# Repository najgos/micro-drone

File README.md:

# DR3 – micro quadcopter with a custom flight controller

A micro quadcopter I designed and built from scratch: my own flight controller PCB designed in KiCad,
flight firmware for the Seeed XIAO ESP32-C6, and a hand-held ESP32 remote linked over ESP-NOW.

**Tech:** KiCad · 2-layer PCB design · C++ · ESP32 / ESP32-C6 · ESP-NOW · MPU6050 over I²C ·
sensor fusion · cascaded PID control

## System overview

| Part | Hardware | Role |
|---|---|---|
| Drone | Custom PCB: Seeed XIAO ESP32-C6, MPU6050 IMU, 4 MOSFET motor channels | Attitude estimation, cascaded PID control, motor PWM, arming logic |
| Remote | ESP32 Dev Module, 2 analog joysticks with ARM / KILL buttons | Reads the sticks and sends control frames over ESP-NOW |

## Hardware – controller PCB

- 2-layer PCB, approx. 45.5 × 51 mm, designed in KiCad (schematic, layout, Gerber files)
- 4 motor channels, each with an N-MOSFET (SOT-23) and an SS14 diode
- Seeed XIAO ESP32-C6 module and MPU6050 (GY-521) IMU over I²C
- 0805 / SOT-23 / SMA footprints; design and production files in [`dr3/`](dr3)

## Firmware

One Arduino sketch for both boards in [`firmware/dr3/`](firmware/dr3). The role is chosen automatically
from the selected board: **XIAO_ESP32C6 → drone**, **ESP32 Dev Module → remote**.

- **Attitude estimation:** gyro and accelerometer fusion in the FRD body frame
- **Control:** angle P loop → angular-rate PID (filtered derivative on measurement, anti-windup), X-frame mixer
- **Arming and stop conditions:** state machine (locked / disarmed / armed / fault); arming only at zero
  throttle with centred sticks; motors stop on KILL, link loss, IMU fault, excessive tilt or USB connection
- **Radio:** ESP-NOW control frames with a project ID and sequence numbers; the drone accepts frames only
  from the first remote it hears and only newer than the previous one
- **Calibration at power-up:** the remote averages the stick centres, the drone averages 200 gyro samples
  to obtain the gyro bias
- **Status LED:** fault, armed, ready to arm, waiting

## Technical details

Built with Arduino-ESP32 3.3.x. Pins, radio settings, IMU mounting and controller gains are in
[`config.h`](firmware/dr3/config.h).

```
firmware/dr3/   drone and remote firmware (C++)
dr3/            KiCad project and Gerber files
docs/images/    photos, flight GIF and the KiCad screenshot
```

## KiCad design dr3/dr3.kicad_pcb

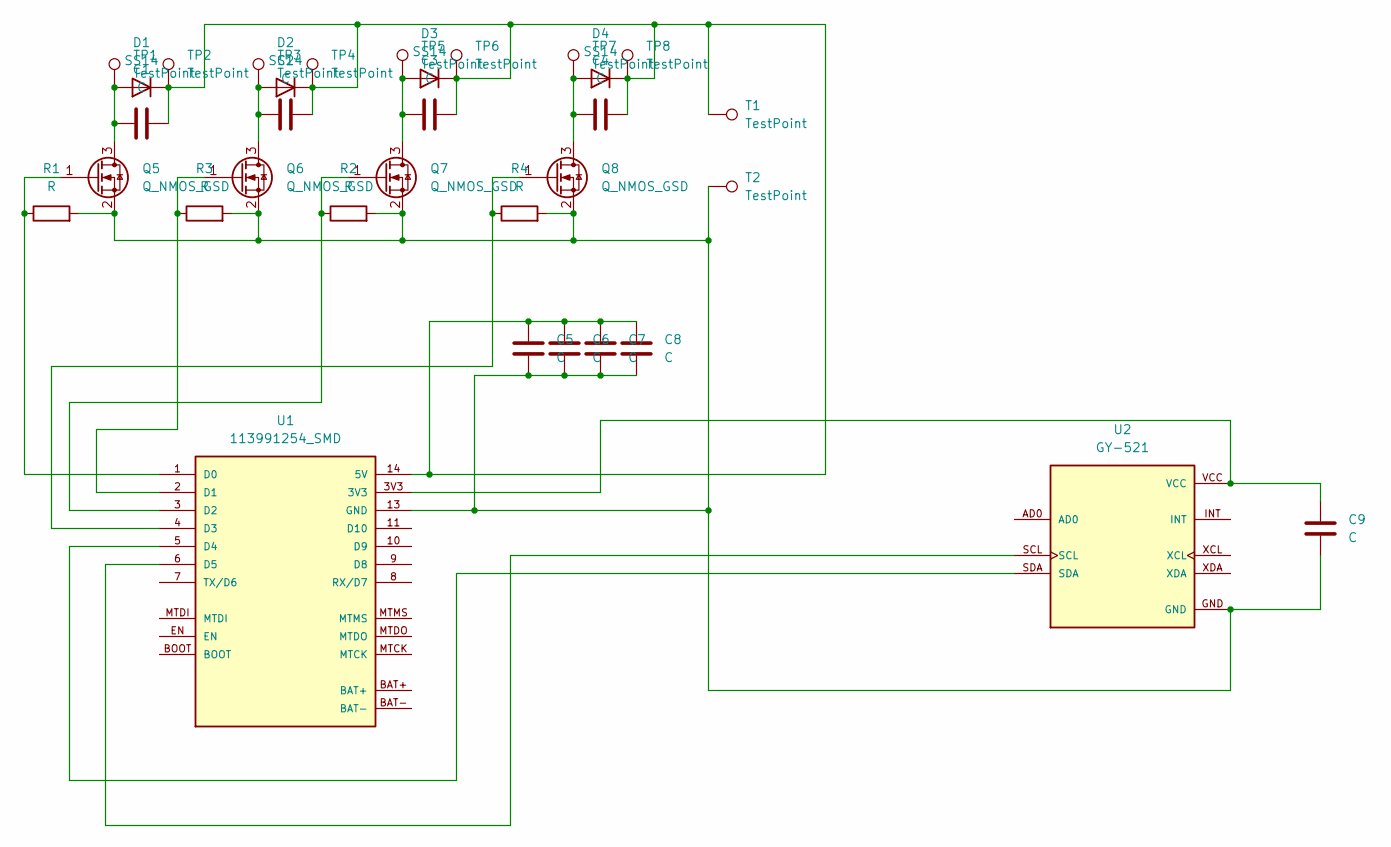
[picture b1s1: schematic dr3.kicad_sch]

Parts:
C1, C2, C3, C4, C5, C6, C7, C8, C9: C; C_0805_2012Metric_Pad1.18x1.45mm_HandSolder
D1, D2, D3, D4: SS14; D_SMA_Handsoldering
Q5, Q6, Q7, Q8: Q_NMOS_GSD; SOT-23_Handsoldering
R1, R2, R3, R4: R; R_0805_2012Metric_Pad1.20x1.40mm_HandSolder
T1, T2: TestPoint; TestPoint_THTPad_2.0x2.0mm_Drill1.0mm
TP1, TP2, TP3, TP4, TP5, TP6, TP7, TP8: TestPoint; TestPoint_THTPad_2.0x2.0mm_Drill1.0mm
U1: 113991254_SMD; esp32-c6; PARTREV 1.0
U2: GY-521; MODULE_GY-521; PARTREV NA

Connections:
3V3: C9.1, U1.3V3, U1.12 (3V3), U2.VCC
GND: C5.2, C6.2, C7.2, C8.2, C9.2, Q5.2 (S), Q6.2 (S), Q7.2 (S), Q8.2 (S), R1.2, R2.2, R3.2, R4.2, T2.1 (1_1), U1.13 (GND), U1.GND, U2.GND
unnamed: C1.1, D1.2 (A), Q5.3 (D), TP1.1 (1_1)
unnamed: C1.2, C2.2, C3.2, C4.2, C5.1, C6.1, C7.1, C8.1, D1.1 (K), D2.1 (K), D3.1 (K), D4.1 (K), T1.1 (1_1), TP2.1 (1_1), TP4.1 (1_1), TP6.1 (1_1), TP8.1 (1_1), U1.14 (5V)
unnamed: C2.1, D2.2 (A), Q6.3 (D), TP3.1 (1_1)
unnamed: C3.1, D3.2 (A), Q7.3 (D), TP5.1 (1_1)
unnamed: C4.1, D4.2 (A), Q8.3 (D), TP7.1 (1_1)
unnamed: Q5.1 (G), R1.1, U1.1 (D0)
unnamed: Q6.1 (G), R3.1, U1.2 (D1)
unnamed: Q7.1 (G), R2.1, U1.3 (D2)
unnamed: Q8.1 (G), R4.1, U1.4 (D3)
unnamed: U1.5 (D4), U2.SDA
unnamed: U1.6 (D5), U2.SCL

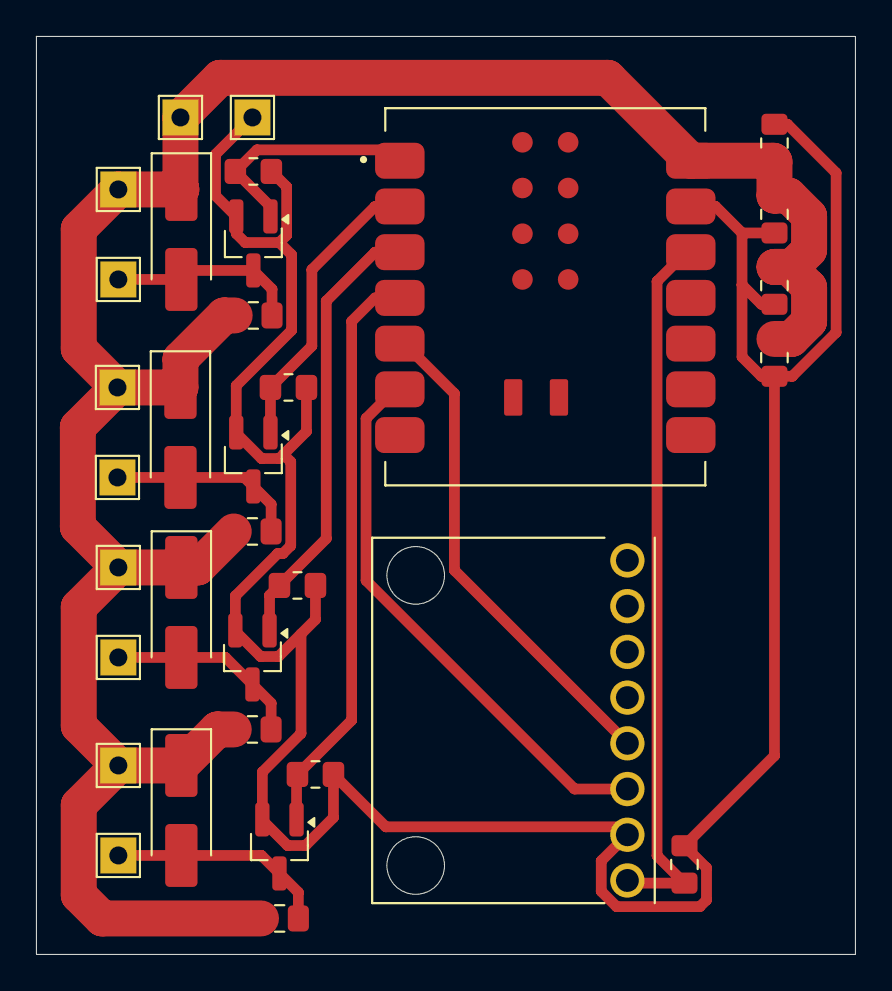
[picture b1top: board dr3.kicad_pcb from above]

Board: 2 copper layers, 45.5 x 51.0 mm, 33 parts (0 on the bottom side), 13 nets.
